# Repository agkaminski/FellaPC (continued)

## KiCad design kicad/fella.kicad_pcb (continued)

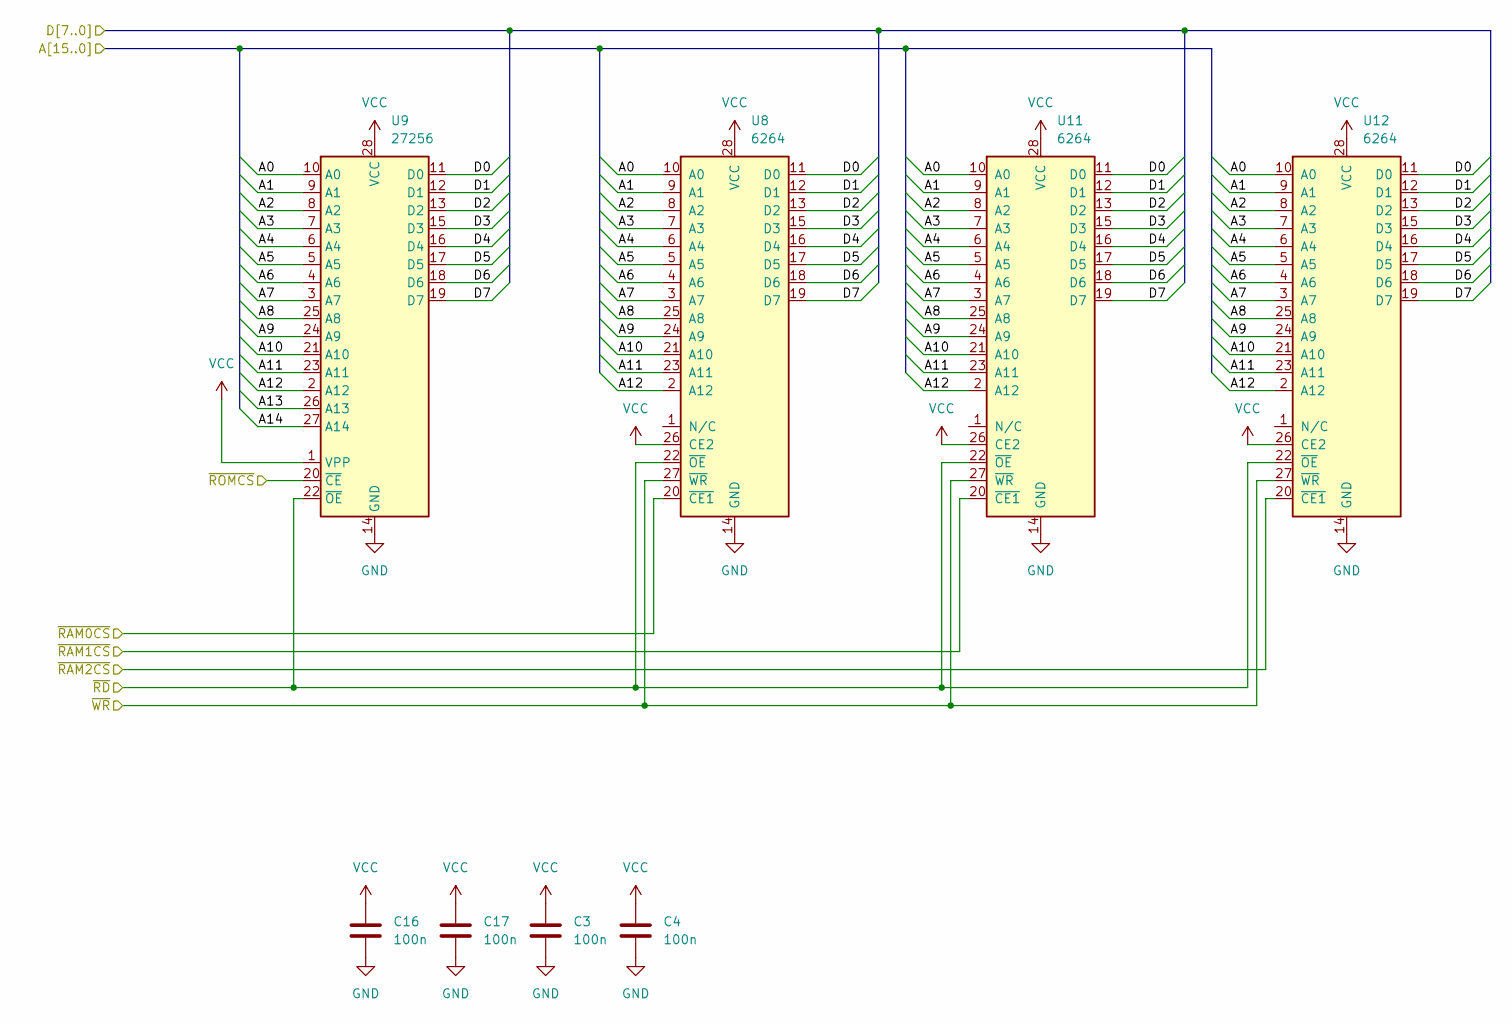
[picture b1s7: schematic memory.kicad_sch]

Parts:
C3, C4, C16, C17: 100n; C_Disc_D5.0mm_W2.5mm_P2.50mm
U8, U11, U12: 6264; DIP-28_W15.24mm
U9: 27256; DIP-28_W15.24mm

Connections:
/cpu/A0: U8.10 (A0), U9.10 (A0), U11.10 (A0), U12.10 (A0); also elsewhere on the board
/cpu/A1: U8.9 (A1), U9.9 (A1), U11.9 (A1), U12.9 (A1); also elsewhere on the board
/cpu/A2: U8.8 (A2), U9.8 (A2), U11.8 (A2), U12.8 (A2); also elsewhere on the board
/cpu/A3: U8.7 (A3), U9.7 (A3), U11.7 (A3), U12.7 (A3); also elsewhere on the board
/cpu/A4: U8.6 (A4), U9.6 (A4), U11.6 (A4), U12.6 (A4); also elsewhere on the board
/cpu/A5: U8.5 (A5), U9.5 (A5), U11.5 (A5), U12.5 (A5); also elsewhere on the board
/cpu/A6: U8.4 (A6), U9.4 (A6), U11.4 (A6), U12.4 (A6); also elsewhere on the board
/cpu/A7: U8.3 (A7), U9.3 (A7), U11.3 (A7), U12.3 (A7); also elsewhere on the board
/cpu/A8: U8.25 (A8), U9.25 (A8), U11.25 (A8), U12.25 (A8); also elsewhere on the board
/cpu/A9: U8.24 (A9), U9.24 (A9), U11.24 (A9), U12.24 (A9); also elsewhere on the board
/cpu/A10: U8.21 (A10), U9.21 (A10), U11.21 (A10), U12.21 (A10); also elsewhere on the board
/cpu/A11: U8.23 (A11), U9.23 (A11), U11.23 (A11), U12.23 (A11); also elsewhere on the board
/cpu/A12: U8.2 (A12), U9.2 (A12), U11.2 (A12), U12.2 (A12); also elsewhere on the board
/cpu/A13: U9.26 (A13); also elsewhere on the board
/cpu/A14: U9.27 (A14); also elsewhere on the board
/cpu/D0: U8.11 (D0), U9.11 (D0), U11.11 (D0), U12.11 (D0); also elsewhere on the board
/cpu/D1: U8.12 (D1), U9.12 (D1), U11.12 (D1), U12.12 (D1); also elsewhere on the board
/cpu/D2: U8.13 (D2), U9.13 (D2), U11.13 (D2), U12.13 (D2); also elsewhere on the board
/cpu/D3: U8.15 (D3), U9.15 (D3), U11.15 (D3), U12.15 (D3); also elsewhere on the board
/cpu/D4: U8.16 (D4), U9.16 (D4), U11.16 (D4), U12.16 (D4); also elsewhere on the board
/cpu/D5: U8.17 (D5), U9.17 (D5), U11.17 (D5), U12.17 (D5); also elsewhere on the board
/cpu/D6: U8.18 (D6), U9.18 (D6), U11.18 (D6), U12.18 (D6); also elsewhere on the board
/cpu/D7: U8.19 (D7), U9.19 (D7), U11.19 (D7), U12.19 (D7); also elsewhere on the board
/cpu/~RAM0CS: U8.20 (~CE1); also elsewhere on the board
/cpu/~RAM1CS: U11.20 (~CE1); also elsewhere on the board
/cpu/~RAM2CS: U12.20 (~CE1); also elsewhere on the board
/cpu/~RD: U8.22 (~OE), U9.22 (~OE), U11.22 (~OE), U12.22 (~OE); also elsewhere on the board
/cpu/~ROMCS: U9.20 (~CE); also elsewhere on the board
/cpu/~WR: U8.27 (~WR), U11.27 (~WR), U12.27 (~WR); also elsewhere on the board
GND: C3.2, C4.2, C16.2, C17.2, U8.14 (GND), U9.14 (GND), U11.14 (GND), U12.14 (GND); also elsewhere on the board
VCC: C3.1, C4.1, C16.1, C17.1, U8.26 (CE2), U8.28 (VCC), U9.1 (VPP), U9.28 (VCC), U11.26 (CE2), U11.28 (VCC), U12.26 (CE2), U12.28 (VCC); also elsewhere on the board

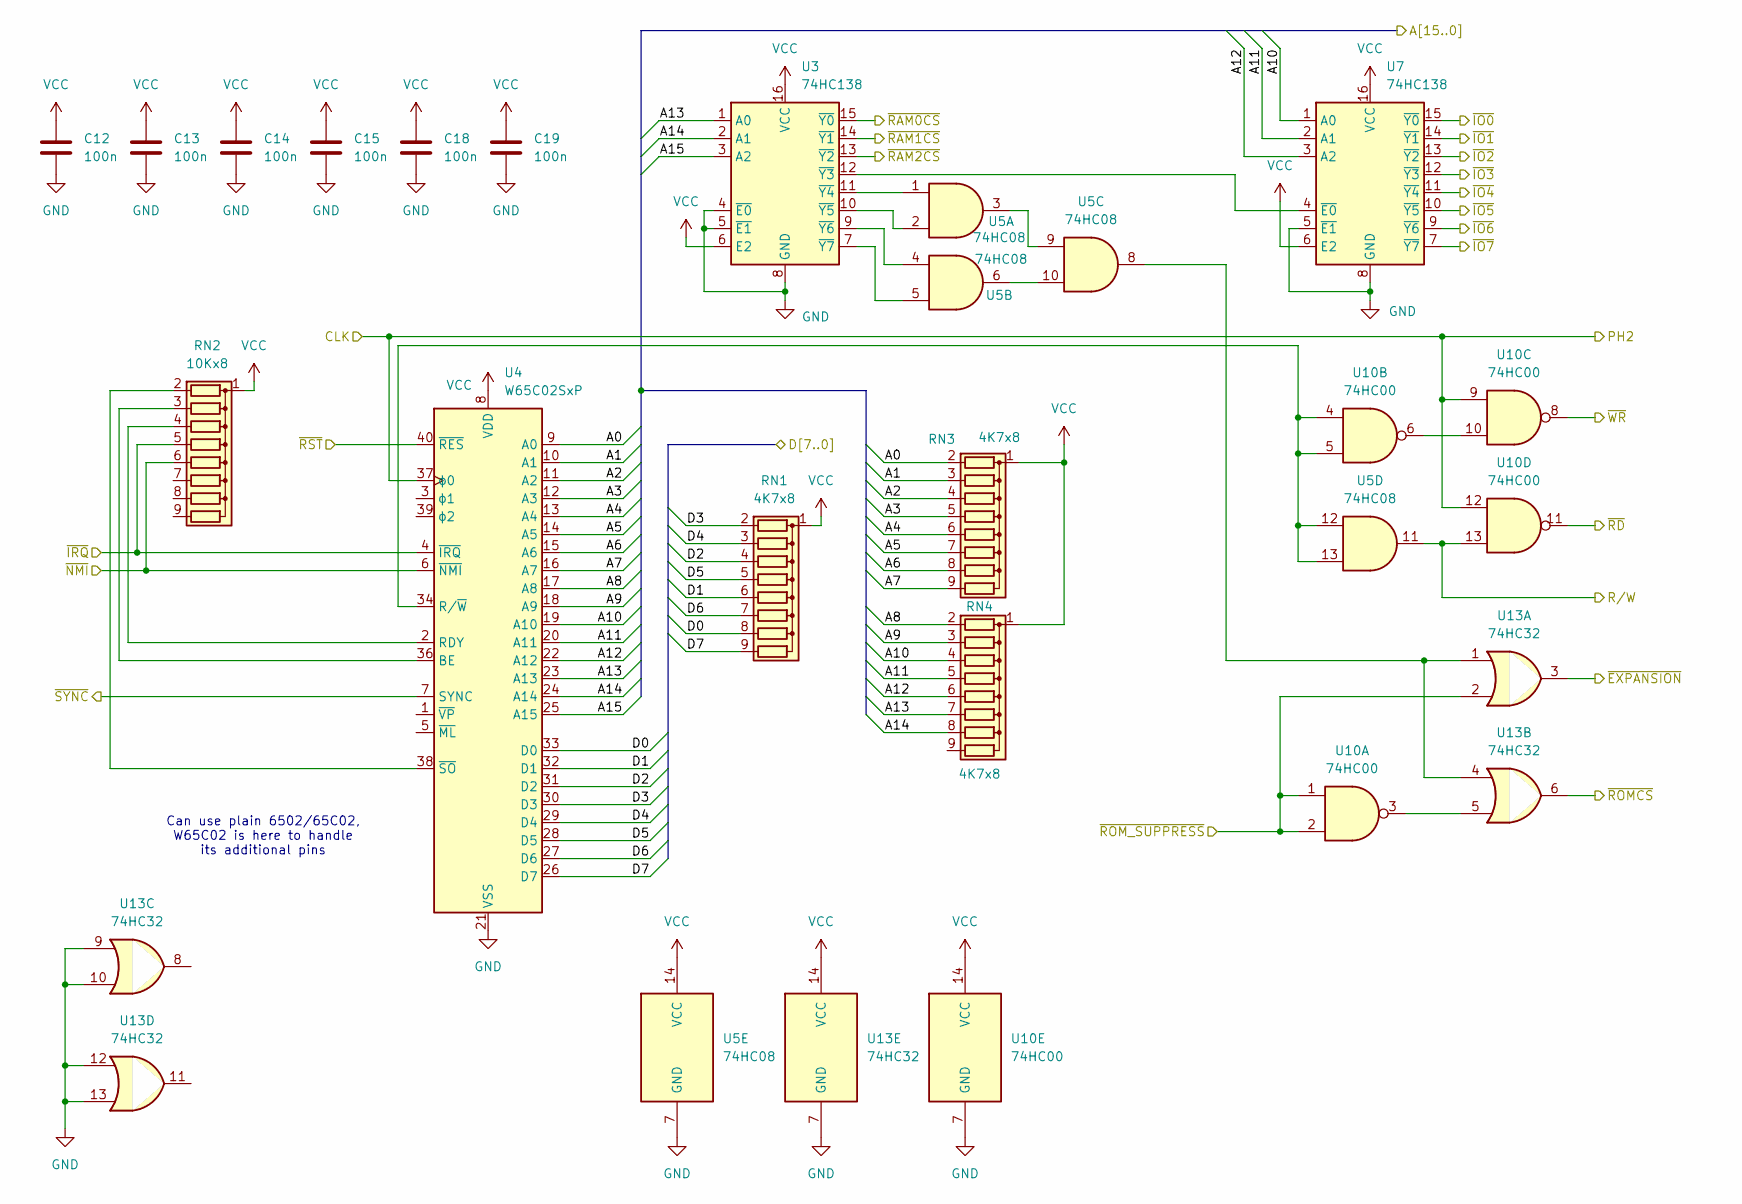
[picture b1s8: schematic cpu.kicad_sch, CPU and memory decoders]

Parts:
C12, C13, C14, C15, C18, C19: 100n; C_Disc_D5.0mm_W2.5mm_P2.50mm
RN1, RN3, RN4: 4K7x8; R_Array_SIP9
RN2: 10Kx8; R_Array_SIP9
U3, U7: 74HC138; DIP-16_W7.62mm
U4: W65C02SxP; DIP-40_W15.24mm
U5: 74HC08; DIP-14_W7.62mm
U10: 74HC00; DIP-14_W7.62mm
U13: 74HC32; DIP-14_W7.62mm

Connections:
/clock/SCLK: U4.37 (ϕ0), U10.9, U10.12; also elsewhere on the board
/clock/~RST: U4.40 (~RES); also elsewhere on the board
/cpu/A0: RN3.2 (R1), U4.9 (A0); also elsewhere on the board
/cpu/A1: RN3.3 (R2), U4.10 (A1); also elsewhere on the board
/cpu/A2: RN3.4 (R3), U4.11 (A2); also elsewhere on the board
/cpu/A3: RN3.5 (R4), U4.12 (A3); also elsewhere on the board
/cpu/A4: RN3.6 (R5), U4.13 (A4); also elsewhere on the board
/cpu/A5: RN3.7 (R6), U4.14 (A5); also elsewhere on the board
/cpu/A6: RN3.8 (R7), U4.15 (A6); also elsewhere on the board
/cpu/A7: RN3.9 (R8), U4.16 (A7); also elsewhere on the board
/cpu/A8: RN4.2 (R1), U4.17 (A8); also elsewhere on the board
/cpu/A9: RN4.3 (R2), U4.18 (A9); also elsewhere on the board
/cpu/A10: RN4.4 (R3), U4.19 (A10), U7.1 (A0); also elsewhere on the board
/cpu/A11: RN4.5 (R4), U4.20 (A11), U7.2 (A1); also elsewhere on the board
/cpu/A12: RN4.6 (R5), U4.22 (A12), U7.3 (A2); also elsewhere on the board
/cpu/A13: RN4.7 (R6), U3.1 (A0), U4.23 (A13); also elsewhere on the board
/cpu/A14: RN4.8 (R7), U3.2 (A1), U4.24 (A14); also elsewhere on the board
/cpu/A15: U3.3 (A2), U4.25 (A15)
/cpu/D0: RN1.8 (R7), U4.33 (D0); also elsewhere on the board
/cpu/D1: RN1.6 (R5), U4.32 (D1); also elsewhere on the board
/cpu/D2: RN1.4 (R3), U4.31 (D2); also elsewhere on the board
/cpu/D3: RN1.2 (R1), U4.30 (D3); also elsewhere on the board
/cpu/D4: RN1.3 (R2), U4.29 (D4); also elsewhere on the board
/cpu/D5: RN1.5 (R4), U4.28 (D5); also elsewhere on the board
/cpu/D6: RN1.7 (R6), U4.27 (D6); also elsewhere on the board
/cpu/D7: RN1.9 (R8), U4.26 (D7); also elsewhere on the board
/cpu/R/W: U5.11, U10.13; also elsewhere on the board
/cpu/~EXPANSION: U13.3; also elsewhere on the board
/cpu/~IO0: U7.15 (~Y0); also elsewhere on the board
/cpu/~IO1: U7.14 (~Y1); also elsewhere on the board
/cpu/~IO2: U7.13 (~Y2); also elsewhere on the board
/cpu/~IO3: U7.12 (~Y3); also elsewhere on the board
/cpu/~IO4: U7.11 (~Y4); also elsewhere on the board
/cpu/~IO5: U7.10 (~Y5); also elsewhere on the board
/cpu/~IO6: U7.9 (~Y6); also elsewhere on the board
/cpu/~IO7: U7.7 (~Y7)
/cpu/~IRQ: RN2.5 (R4), U4.4 (~IRQ); also elsewhere on the board
/cpu/~NMI: RN2.6 (R5), U4.6 (~NMI); also elsewhere on the board
/cpu/~RAM0CS: U3.15 (~Y0); also elsewhere on the board
/cpu/~RAM1CS: U3.14 (~Y1); also elsewhere on the board
/cpu/~RAM2CS: U3.13 (~Y2); also elsewhere on the board
/cpu/~RD: U10.11; also elsewhere on the board
/cpu/~ROMCS: U13.6; also elsewhere on the board
/cpu/~ROM_SUPPRESS: U10.1, U10.2, U13.2; also elsewhere on the board
/cpu/~SYNC: U4.7 (SYNC)
/cpu/~WR: U10.8; also elsewhere on the board
GND: C12.2, C13.2, C14.2, C15.2, C18.2, C19.2, U3.4 (~E0), U3.5 (~E1), U3.8 (GND), U4.21 (VSS), U5.7 (GND), U7.5 (~E1), U7.8 (GND), U10.7 (GND), U13.7 (GND), U13.9, U13.10, U13.12, U13.13; also elsewhere on the board
unnamed: RN2.2 (R1), U4.38 (~SO)
unnamed: RN2.3 (R2), U4.36 (BE)
unnamed: RN2.4 (R3), U4.2 (RDY)
unnamed: U3.12 (~Y3), U7.4 (~E0)
unnamed: U3.11 (~Y4), U5.1
unnamed: U3.10 (~Y5), U5.2
unnamed: U3.9 (~Y6), U5.4
unnamed: U3.7 (~Y7), U5.5
unnamed: U4.34 (R/~W), U5.12, U5.13, U10.4, U10.5
unnamed: U5.3, U5.9
unnamed: U5.6, U5.10
unnamed: U10.3, U13.5
unnamed: U10.6, U10.10
unnamed: U5.8, U13.1, U13.4
VCC: C12.1, C13.1, C14.1, C15.1, C18.1, C19.1, RN1.1 (common), RN2.1 (common), RN3.1 (common), RN4.1 (common), U3.6 (E2), U3.16 (VCC), U4.8 (VDD), U5.14 (VCC), U7.6 (E2), U7.16 (VCC), U10.14 (VCC), U13.14 (VCC); also elsewhere on the board

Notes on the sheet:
Can use plain 6502/65C02, W65C02 is here to handle its additional pins

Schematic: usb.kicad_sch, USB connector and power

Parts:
C8, C44: 100n; C_Disc_D5.0mm_W2.5mm_P2.50mm
C48, C49: 470u; CP_Radial_D10.0mm_P5.00mm
J3: USB_C_Receptacle_USB2.0_14P; USB_C_Receptacle_G-Switch_GT-USB-7010ASV
R5, R6: 1K5; R_Axial_DIN0207_L6.3mm_D2.5mm_P7.62mm_Horizontal
U33: CH340N; SOP-8_3.9x4.9mm_P1.27mm

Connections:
/io/RX: U33.6 (TXD); also elsewhere on the board
/io/TX: U33.7 (RXD); also elsewhere on the board
GND: C8.2, C44.2, C48.2, C49.2, J3.A1 (GND), J3.A12 (GND), J3.B1 (GND), J3.B12 (GND), J3.S1 (SHIELD), R5.2, R6.2, U33.3 (GND); also elsewhere on the board
unnamed: J3.A5 (CC1), R6.1
unnamed: J3.B5 (CC2), R5.1
unnamed: J3.A6 (D+), J3.B6 (D+), U33.1 (UD+)
unnamed: J3.A7 (D-), J3.B7 (D-), U33.2 (UD-)
unnamed: C8.1, U33.8 (V3)
VCC: C44.1, C48.1, C49.1, J3.A4 (VBUS), J3.A9 (VBUS), J3.B4 (VBUS), J3.B9 (VBUS), U33.5 (VCC); also elsewhere on the board

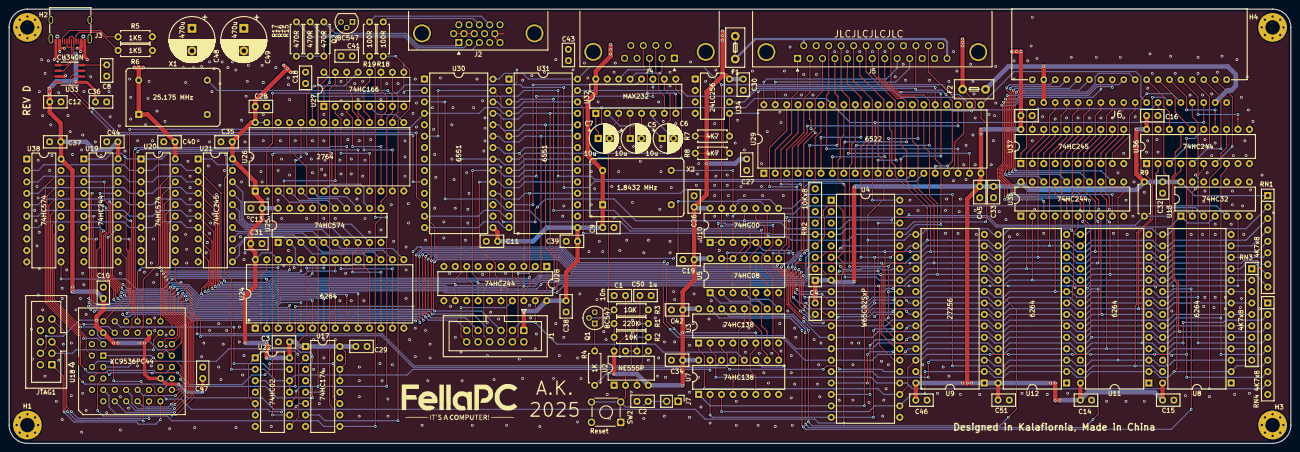
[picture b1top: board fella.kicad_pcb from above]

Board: 2 copper layers, 284.9 x 96.5 mm, 114 parts (0 on the bottom side), 206 nets.

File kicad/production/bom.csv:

Designator,Footprint,Quantity,Value,LCSC Part #
C1,C_Disc_D5.0mm_W2.5mm_P2.50mm,1,10n,
"C10, C11, C12, C13, C14, C15, C16, C17, C18, C19, C2, C26, C27, C28, C29, C3, C30, C31, C32, C33, C34, C35, C36, C37, C38, C39, C4, C40, C41, C42, C43, C44, C45, C46, C47, C51, C8, C9",C_Disc_D5.0mm_W2.5mm_P2.50mm,38,100n,
"C48, C49",CP_Radial_D10.0mm_P5.00mm,2,470u,
"C5, C6, C7",CP_Radial_D6.3mm_P2.50mm,3,10u,
C50,C_Disc_D5.0mm_W2.5mm_P2.50mm,1,1u,
"F1, F2",Fuse_Littelfuse_395Series,2,Fuse,
"H1, H2, H3, H4",MountingHole_3.2mm_M3_Pad_Via,4,MountingHole_Pad,
J1,IDC-Header_2x06_P2.54mm_Vertical,1,Conn_02x06_Odd_Even,
J2,DSUB-15-HD_Female_Horizontal_P2.29x1.98mm_EdgePinOffset3.03mm_Housed_MountingHolesOffset4.94mm,1,DE15_Receptacle_HighDensity_MountingHoles,
J3,USB_C_Receptacle_G-Switch_GT-USB-7010ASV,1,USB_C_Receptacle_USB2.0_14P,
J4,DSUB-9_Male_Horizontal_P2.77x2.84mm_EdgePinOffset7.70mm_Housed_MountingHolesOffset9.12mm,1,DE9_Plug_MountingHoles,
J5,DSUB-25_Socket_Horizontal_P2.77x2.84mm_EdgePinOffset7.70mm_Housed_MountingHolesOffset9.12mm,1,DB25_Receptacle_MountingHoles,
J6,EDGE_2x18,1,Conn_02x18_Top_Bottom,
J7,PinHeader_1x02_P2.54mm_Vertical,1,Conn_01x02,
JTAG1,IDC-Header_2x05_P2.54mm_Vertical,1,Conn_02x05_Odd_Even,
"Q1, Q2",TO-92,2,BC547,
R1,R_Axial_DIN0207_L6.3mm_D2.5mm_P7.62mm_Horizontal,1,220K,
"R15, R16, R17",R_Axial_DIN0207_L6.3mm_D2.5mm_P7.62mm_Horizontal,3,470R,
"R18, R19",R_Axial_DIN0207_L6.3mm_D2.5mm_P7.62mm_Horizontal,2,100R,
"R2, R3",R_Axial_DIN0207_L6.3mm_D2.5mm_P7.62mm_Horizontal,2,10K,
R4,R_Axial_DIN0207_L6.3mm_D2.5mm_P7.62mm_Horizontal,1,1K,
"R5, R6",R_Axial_DIN0207_L6.3mm_D2.5mm_P7.62mm_Horizontal,2,1K5,
"R7, R8, R9",R_Axial_DIN0207_L6.3mm_D2.5mm_P7.62mm_Horizontal,3,4K7,
"RN1, RN3, RN4",R_Array_SIP9,3,4K7x8,
RN2,R_Array_SIP9,1,10Kx8,
SW2,SW_TH_Tactile_Omron_B3F-10xx,1,Reset,
U10,DIP-14_W7.62mm,1,74HC00,
"U11, U12, U24, U8",DIP-28_W15.24mm,4,6264,
U13,DIP-14_W7.62mm,1,74HC32,
U17,DIP-16_W7.62mm,1,74HC174,
U18,PLCC-44_THT-Socket,1,XC9536PC44,
"U19, U28, U35, U36",DIP-20_W7.62mm,4,74HC244,
U2,DIP-8_W7.62mm,1,NE555P,
"U20, U25, U38",DIP-20_W7.62mm,3,74HC574,
"U21, U37",DIP-20_W7.62mm,2,74HC245,
U22,DIP-14_W7.62mm,1,74HC02,
U26,DIP-28_W15.24mm,1,2764,
U27,DIP-16_W7.62mm,1,74HC166,
U29,DIP-40_W15.24mm,1,6522,
"U3, U7",DIP-16_W7.62mm,2,74HC138,
"U30, U31",DIP-28_W15.24mm,2,6551,
U32,DIP-16_W7.62mm,1,MAX232,
U33,SOP-8_3.9x4.9mm_P1.27mm,1,CH340N,
U34,DIP-8_W7.62mm,1,24LC256,
U4,DIP-40_W15.24mm,1,W65C02SxP,
U5,DIP-14_W7.62mm,1,74HC08,
U9,DIP-28_W15.24mm,1,27256,
X1,Oscillator_DIP-14,1,ACO-25.175MHz-A,
X2,Oscillator_DIP-14,1,ACO-1.8432MHz-A,

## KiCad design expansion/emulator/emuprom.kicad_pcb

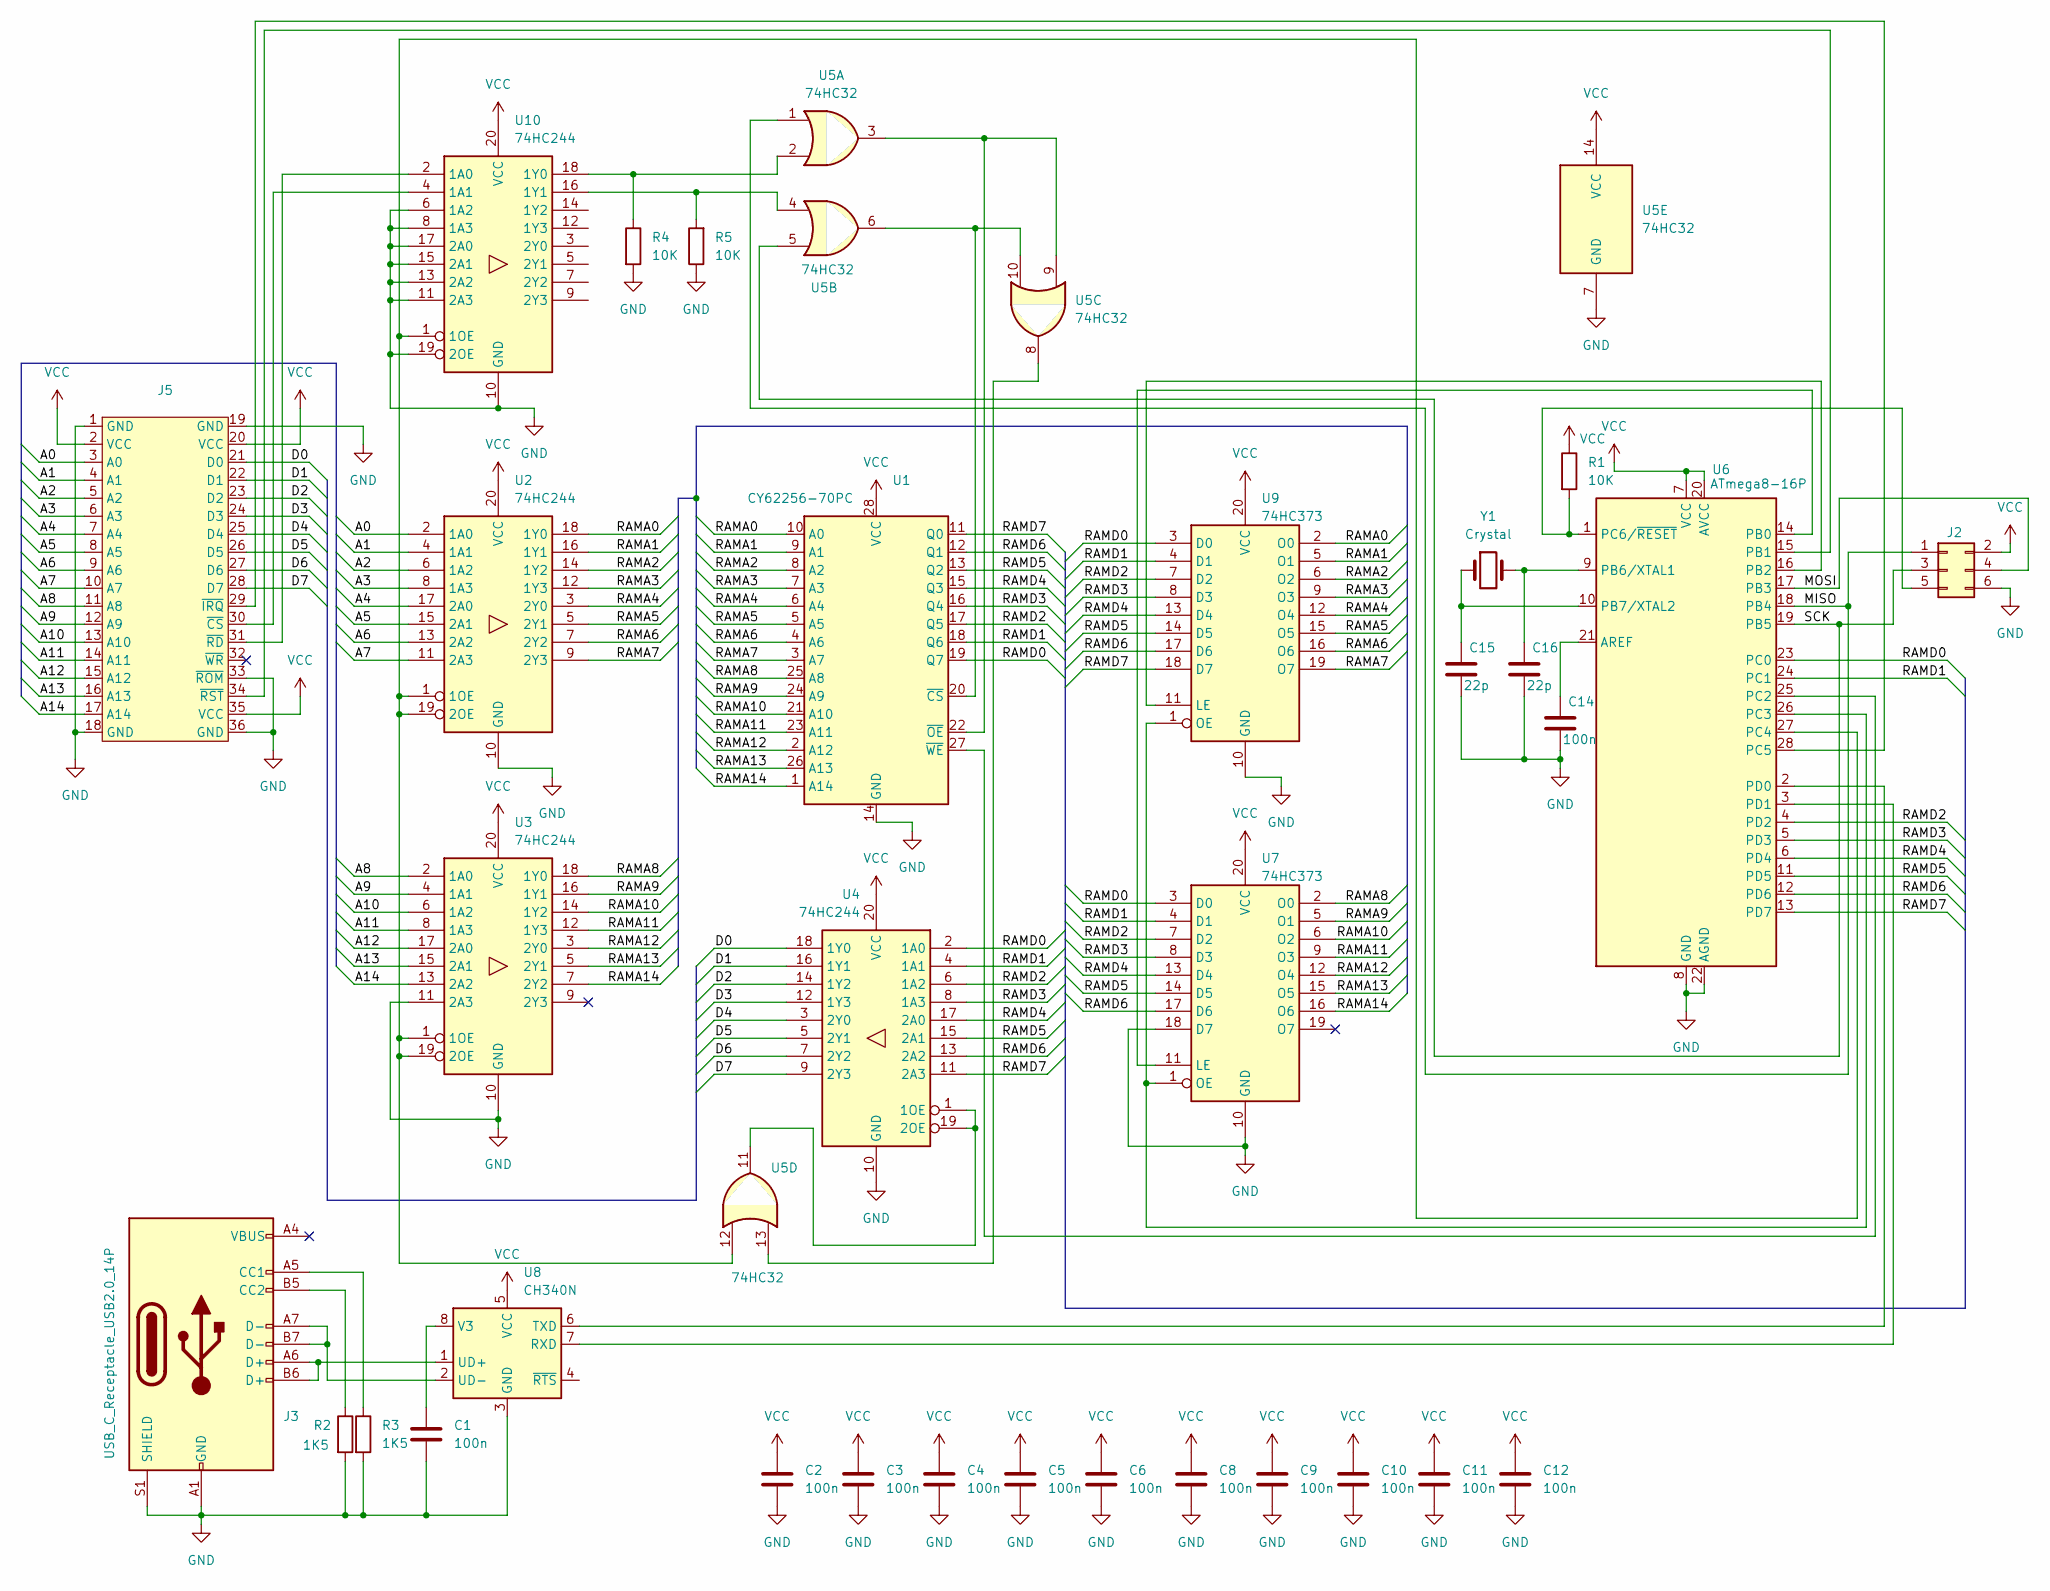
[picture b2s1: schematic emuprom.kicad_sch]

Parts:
C1, C2, C3, C4, C5, C6, C8, C9, C10, C11, C12, C14: 100n; C_Disc_D3.0mm_W1.6mm_P2.50mm
C15, C16: 22p; C_Disc_D3.0mm_W1.6mm_P2.50mm
J2: Conn_02x03_Odd_Even; IDC-Header_2x03_P2.54mm_Vertical
J3: USB_C_Receptacle_USB2.0_14P; USB_C_Receptacle_GCT_USB4105-xx-A_16P_TopMnt_Horizontal
J5: Expansion Connector
R1, R4, R5: 10K; R_Axial_DIN0207_L6.3mm_D2.5mm_P7.62mm_Horizontal
R2, R3: 1K5; R_Axial_DIN0207_L6.3mm_D2.5mm_P7.62mm_Horizontal
U1: CY62256-70PC; DIP-28_W15.24mm
U2, U3, U4, U10: 74HC244; DIP-20_W7.62mm
U5: 74HC32; DIP-14_W7.62mm
U6: ATmega8-16P; DIP-28_W7.62mm
U7, U9: 74HC373; DIP-20_W7.62mm
U8: CH340N; SOP-8_3.9x4.9mm_P1.27mm
Y1: Crystal; Crystal_HC49-4H_Vertical

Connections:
/A0: J5.3 (A0), U2.2 (1A0)
/A1: J5.4 (A1), U2.4 (1A1)
/A2: J5.5 (A2), U2.6 (1A2)
/A3: J5.6 (A3), U2.8 (1A3)
/A4: J5.7 (A4), U2.17 (2A0)
/A5: J5.8 (A5), U2.15 (2A1)
/A6: J5.9 (A6), U2.13 (2A2)
/A7: J5.10 (A7), U2.11 (2A3)
/A8: J5.11 (A8), U3.2 (1A0)
/A9: J5.12 (A9), U3.4 (1A1)
/A10: J5.13 (A10), U3.6 (1A2)
/A11: J5.14 (A11), U3.8 (1A3)
/A12: J5.15 (A12), U3.17 (2A0)
/A13: J5.16 (A13), U3.15 (2A1)
/A14: J5.17 (A14), U3.13 (2A2)
/D0: J5.21 (D0), U4.18 (1Y0)
/D1: J5.22 (D1), U4.16 (1Y1)
/D2: J5.23 (D2), U4.14 (1Y2)
/D3: J5.24 (D3), U4.12 (1Y3)
/D4: J5.25 (D4), U4.3 (2Y0)
/D5: J5.26 (D5), U4.5 (2Y1)
/D6: J5.27 (D6), U4.7 (2Y2)
/D7: J5.28 (D7), U4.9 (2Y3)
/MISO: J2.1, U5.1, U6.18 (PB4)
/MOSI: J2.4, U6.17 (PB3)
/RAMA0: U1.10 (A0), U2.18 (1Y0), U9.2 (O0)
/RAMA1: U1.9 (A1), U2.16 (1Y1), U9.5 (O1)
/RAMA2: U1.8 (A2), U2.14 (1Y2), U9.6 (O2)
/RAMA3: U1.7 (A3), U2.12 (1Y3), U9.9 (O3)
/RAMA4: U1.6 (A4), U2.3 (2Y0), U9.12 (O4)
/RAMA5: U1.5 (A5), U2.5 (2Y1), U9.15 (O5)
/RAMA6: U1.4 (A6), U2.7 (2Y2), U9.16 (O6)
/RAMA7: U1.3 (A7), U2.9 (2Y3), U9.19 (O7)
/RAMA8: U1.25 (A8), U3.18 (1Y0), U7.2 (O0)
/RAMA9: U1.24 (A9), U3.16 (1Y1), U7.5 (O1)
/RAMA10: U1.21 (A10), U3.14 (1Y2), U7.6 (O2)
/RAMA11: U1.23 (A11), U3.12 (1Y3), U7.9 (O3)
/RAMA12: U1.2 (A12), U3.3 (2Y0), U7.12 (O4)
/RAMA13: U1.26 (A13), U3.5 (2Y1), U7.15 (O5)
/RAMA14: U1.1 (A14), U3.7 (2Y2), U7.16 (O6)
/RAMD0: U1.19 (Q7), U4.2 (1A0), U6.23 (PC0), U7.3 (D0), U9.3 (D0)
/RAMD1: U1.18 (Q6), U4.4 (1A1), U6.24 (PC1), U7.4 (D1), U9.4 (D1)
/RAMD2: U1.17 (Q5), U4.6 (1A2), U6.4 (PD2), U7.7 (D2), U9.7 (D2)
/RAMD3: U1.16 (Q4), U4.8 (1A3), U6.5 (PD3), U7.8 (D3), U9.8 (D3)
/RAMD4: U1.15 (Q3), U4.17 (2A0), U6.6 (PD4), U7.13 (D4), U9.13 (D4)
/RAMD5: U1.13 (Q2), U4.15 (2A1), U6.11 (PD5), U7.14 (D5), U9.14 (D5)
/RAMD6: U1.12 (Q1), U4.13 (2A2), U6.12 (PD6), U7.17 (D6), U9.17 (D6)
/RAMD7: U1.11 (Q0), U4.11 (2A3), U6.13 (PD7), U9.18 (D7)
/SCK: J2.3, U5.5, U6.19 (PB5)
GND: C1.2, C2.2, C3.2, C4.2, C5.2, C6.2, C8.2, C9.2, C10.2, C11.2, C12.2, C14.2, C15.2, C16.2, J2.6, J3.A1 (GND), J3.A12 (GND), J3.B1 (GND), J3.B12 (GND), J3.S1 (SHIELD), J5.1 (GND), J5.18 (GND), J5.19 (GND), J5.33 (~ROM), J5.36 (GND), R2.2, R3.2, R4.2, R5.1, U1.14 (GND), U2.10 (GND), U3.10 (GND), U3.11 (2A3), U4.10 (GND), U5.7 (GND), U6.8 (GND), U6.22 (AGND), U7.10 (GND), U7.18 (D7), U8.3 (GND), U9.10 (GND), U10.6 (1A2), U10.8 (1A3), U10.10 (GND), U10.11 (2A3), U10.13 (2A2), U10.15 (2A1), U10.17 (2A0), U10.19 (2OE)
unnamed: J2.5, R1.2, U6.1 (PC6/~RESET)
unnamed: J3.A5 (CC1), R3.1
unnamed: J3.B5 (CC2), R2.1
unnamed: J5.30 (~CS), U10.4 (1A1)
unnamed: J5.29 (~IRQ), U6.28 (PC5)
unnamed: J5.31 (~RD), U10.2 (1A0)
unnamed: J5.34 (~RST), U6.15 (PB1)
unnamed: U1.20 (~CS), U5.6, U5.10
unnamed: U1.22 (~OE), U5.3, U5.9
unnamed: U1.27 (~WE), U6.25 (PC2)
unnamed: U4.1 (1OE), U4.19 (2OE), U5.11
unnamed: U5.8, U5.13
unnamed: C14.1, U6.21 (AREF)
unnamed: U6.14 (PB0), U7.11 (LE)
unnamed: U6.16 (PB2), U9.11 (LE)
unnamed: C16.1, U6.9 (PB6/XTAL1), Y1.2
unnamed: C15.1, U6.10 (PB7/XTAL2), Y1.1
unnamed: U6.26 (PC3), U7.1 (OE), U9.1 (OE)
unnamed: U6.2 (PD0), U8.6 (TXD)
unnamed: U6.3 (PD1), U8.7 (RXD)
unnamed: J3.A6 (D+), J3.B6 (D+), U8.1 (UD+)
unnamed: J3.A7 (D-), J3.B7 (D-), U8.2 (UD-)
unnamed: C1.1, U8.8 (V3)
unnamed: U2.1 (1OE), U2.19 (2OE), U3.1 (1OE), U3.19 (2OE), U5.12, U6.27 (PC4), U10.1 (1OE)
unnamed: R4.1, U5.2, U10.18 (1Y0)
unnamed: R5.2, U5.4, U10.16 (1Y1)
VCC: C2.1, C3.1, C4.1, C5.1, C6.1, C8.1, C9.1, C10.1, C11.1, C12.1, J2.2, J5.2 (VCC), J5.20 (VCC), J5.35 (VCC), R1.1, U1.28 (VCC), U2.20 (VCC), U3.20 (VCC), U4.20 (VCC), U5.14 (VCC), U6.7 (VCC), U6.20 (AVCC), U7.20 (VCC), U8.5 (VCC), U9.20 (VCC), U10.20 (VCC)

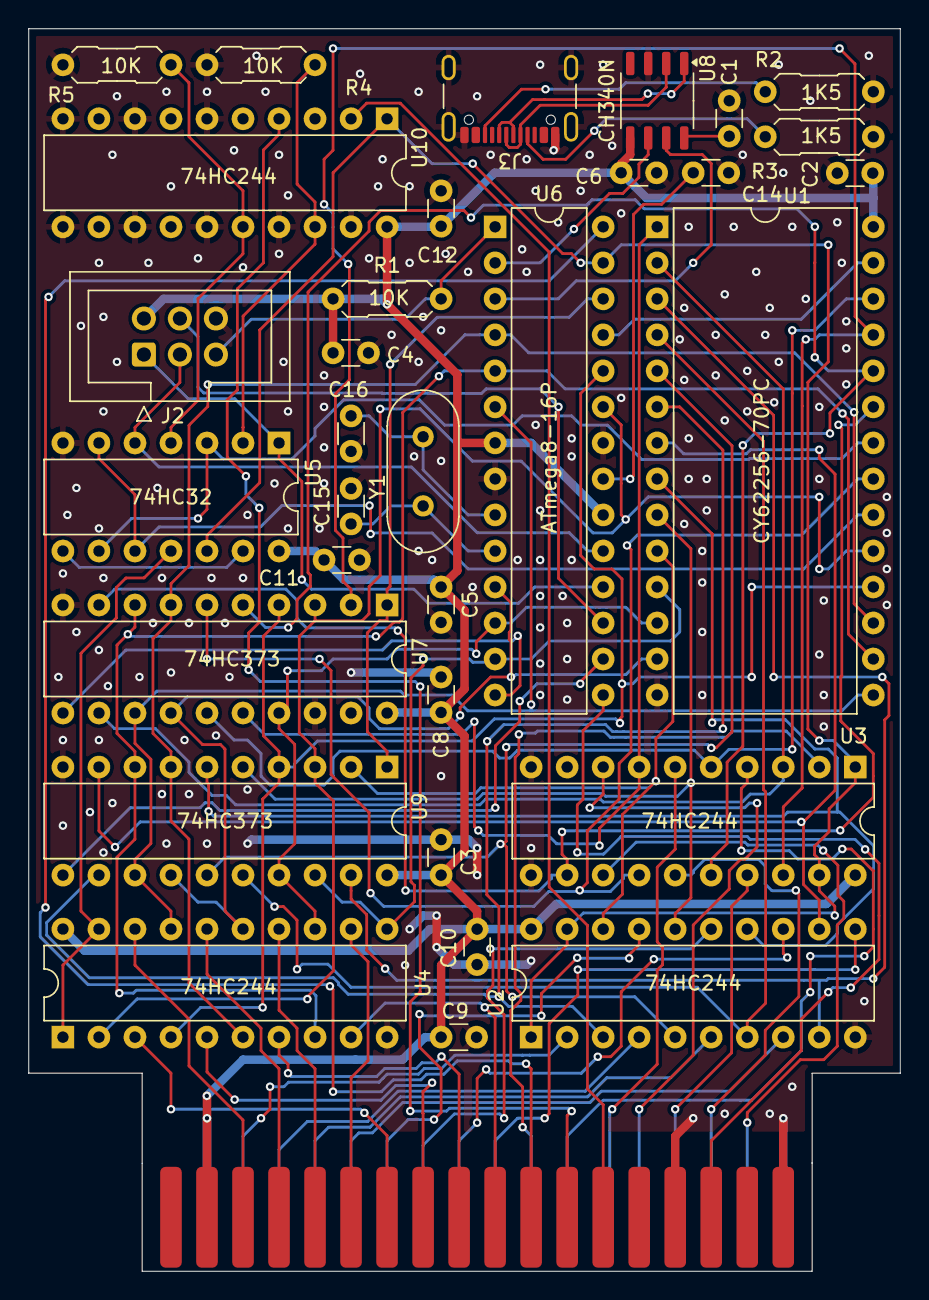
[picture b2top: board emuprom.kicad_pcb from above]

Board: 2 copper layers, 61.5 x 87.6 mm, 33 parts (0 on the bottom side), 77 nets.

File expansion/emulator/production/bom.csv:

Designator,Footprint,Quantity,Value,LCSC Part #
"C1, C10, C11, C12, C14, C2, C3, C4, C5, C6, C8, C9",C_Disc_D3.0mm_W1.6mm_P2.50mm,12,100n,
"C15, C16",C_Disc_D3.0mm_W1.6mm_P2.50mm,2,22p,
J2,IDC-Header_2x03_P2.54mm_Vertical,1,Conn_02x03_Odd_Even,
J3,USB_C_Receptacle_GCT_USB4105-xx-A_16P_TopMnt_Horizontal,1,USB_C_Receptacle_USB2.0_14P,
J5,Expansion Connector,1,~,
"R1, R4, R5",R_Axial_DIN0207_L6.3mm_D2.5mm_P7.62mm_Horizontal,3,10K,
"R2, R3",R_Axial_DIN0207_L6.3mm_D2.5mm_P7.62mm_Horizontal,2,1K5,
U1,DIP-28_W15.24mm,1,CY62256-70PC,
"U10, U2, U3, U4",DIP-20_W7.62mm,4,74HC244,
U5,DIP-14_W7.62mm,1,74HC32,
U6,DIP-28_W7.62mm,1,ATmega8-16P,
"U7, U9",DIP-20_W7.62mm,2,74HC373,
U8,SOP-8_3.9x4.9mm_P1.27mm,1,CH340N,
Y1,Crystal_HC49-4H_Vertical,1,Crystal,

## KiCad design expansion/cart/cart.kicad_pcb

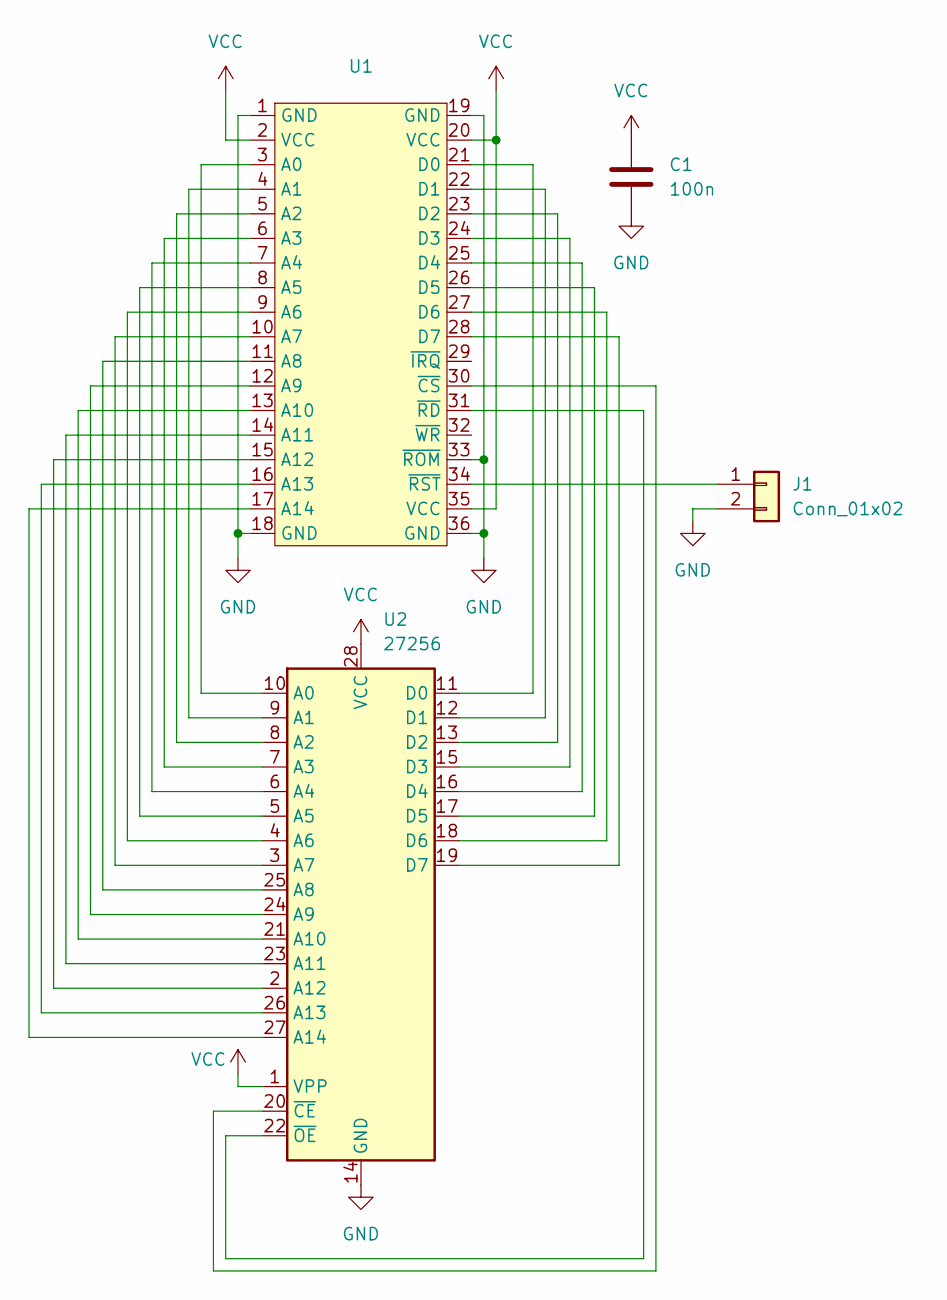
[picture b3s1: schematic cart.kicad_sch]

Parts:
C1: 100n; C_Disc_D3.4mm_W2.1mm_P2.50mm
J1: Conn_01x02; PinHeader_1x02_P2.54mm_Vertical
U1: CART_FELLA_38
U2: 27256; DIP-28_W15.24mm

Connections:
GND: C1.2, J1.2, U1.1 (GND), U1.18 (GND), U1.19 (GND), U1.33 (~ROM), U1.36 (GND), U2.14 (GND)
unnamed: J1.1, U1.34 (~RST)
unnamed: U1.3 (A0), U2.10 (A0)
unnamed: U1.4 (A1), U2.9 (A1)
unnamed: U1.5 (A2), U2.8 (A2)
unnamed: U1.6 (A3), U2.7 (A3)
unnamed: U1.7 (A4), U2.6 (A4)
unnamed: U1.8 (A5), U2.5 (A5)
unnamed: U1.9 (A6), U2.4 (A6)
unnamed: U1.10 (A7), U2.3 (A7)
unnamed: U1.11 (A8), U2.25 (A8)
unnamed: U1.12 (A9), U2.24 (A9)
unnamed: U1.13 (A10), U2.21 (A10)
unnamed: U1.14 (A11), U2.23 (A11)
unnamed: U1.15 (A12), U2.2 (A12)
unnamed: U1.16 (A13), U2.26 (A13)
unnamed: U1.17 (A14), U2.27 (A14)
unnamed: U1.21 (D0), U2.11 (D0)
unnamed: U1.22 (D1), U2.12 (D1)
unnamed: U1.23 (D2), U2.13 (D2)
unnamed: U1.24 (D3), U2.15 (D3)
unnamed: U1.25 (D4), U2.16 (D4)
unnamed: U1.26 (D5), U2.17 (D5)
unnamed: U1.27 (D6), U2.18 (D6)
unnamed: U1.28 (D7), U2.19 (D7)
unnamed: U1.30 (~CS), U2.20 (~CE)
unnamed: U1.31 (~RD), U2.22 (~OE)
VCC: C1.1, U1.2 (VCC), U1.20 (VCC), U1.35 (VCC), U2.1 (VPP), U2.28 (VCC)

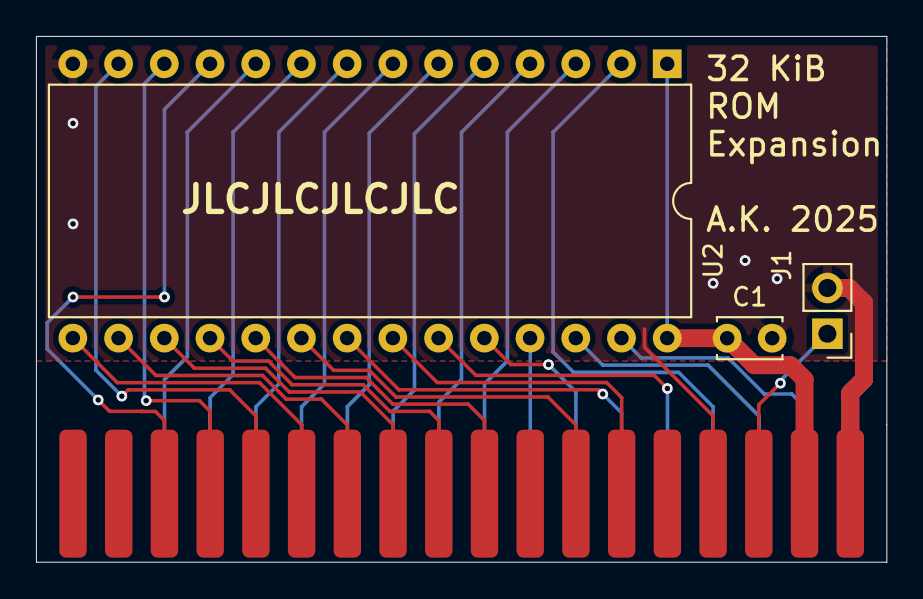
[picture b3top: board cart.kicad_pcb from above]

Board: 2 copper layers, 47.2 x 29.2 mm, 4 parts (0 on the bottom side), 28 nets.

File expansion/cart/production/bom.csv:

Designator,Footprint,Quantity,Value,LCSC Part #
C1,C_Disc_D3.4mm_W2.1mm_P2.50mm,1,100n,
J1,PinHeader_1x02_P2.54mm_Vertical,1,Conn_01x02,
U1,CART_FELLA_38,1,~,
U2,DIP-28_W15.24mm,1,27256,

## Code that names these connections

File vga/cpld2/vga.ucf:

#PACE: Start of Constraints generated by PACE

#PACE: Start of PACE I/O Pin Assignments
NET "blank"  LOC = "P3"  ; 
NET "col<3>"  LOC = "P18"  ; 
NET "col<4>"  LOC = "P14"  ; 
NET "col<5>"  LOC = "P13"  ; 
NET "col<6>"  LOC = "P12"  ; 
NET "col<7>"  LOC = "P11"  ; 
NET "col<8>"  LOC = "P9"  ; 
NET "col<9>"  LOC = "P8"  ; 
NET "hsync"  LOC = "P2"  ; 
NET "oe_n"  LOC = "P37"  ; 
NET "pclk"  LOC = "P5"  ; 
NET "row<0>"  LOC = "P36"  ; 
NET "row<1>"  LOC = "P35"  ; 
NET "row<2>"  LOC = "P34"  ; 
NET "row<3>"  LOC = "P33"  ; 
NET "row<4>"  LOC = "P29"  ; 
NET "row<5>"  LOC = "P28"  ; 
NET "row<6>"  LOC = "P27"  ; 
NET "row<7>"  LOC = "P26"  ; 
NET "row<8>"  LOC = "P25"  ; 
NET "rst_n"  LOC = "P39"  ; 
NET "shload_n"  LOC = "P4"  ; 
NET "vsync"  LOC = "P1"  ; 

#PACE: Start of PACE Area Constraints

#PACE: Start of PACE Prohibit Constraints

#PACE: End of Constraints generated by PACE
